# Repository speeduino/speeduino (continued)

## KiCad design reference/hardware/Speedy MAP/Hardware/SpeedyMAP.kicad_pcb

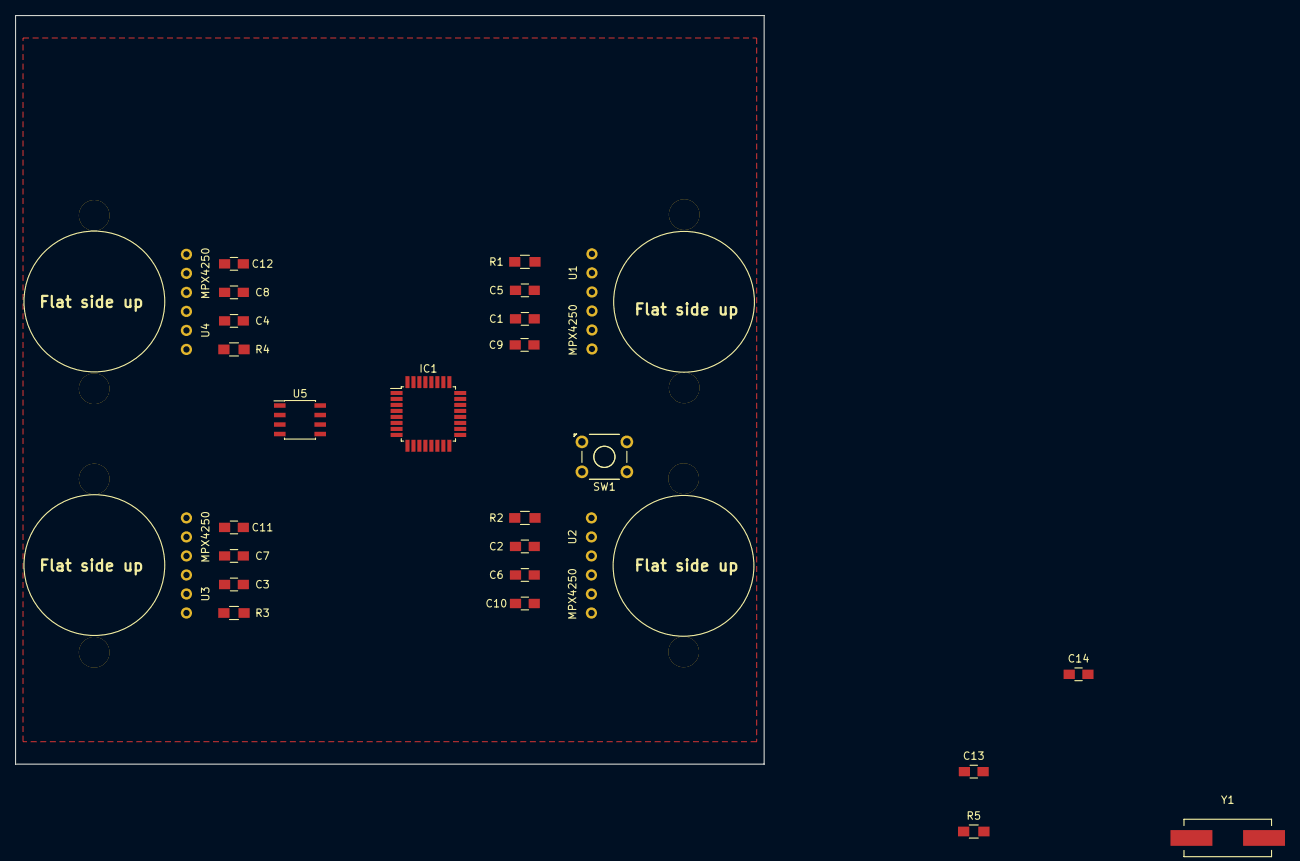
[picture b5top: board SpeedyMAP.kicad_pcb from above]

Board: 2 copper layers, 100.0 x 100.0 mm, 27 parts (0 on the bottom side), 16 nets, no tracks yet.

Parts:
C1, C2, C3, C4: C1uF; C_0805_HandSoldering
C5, C6, C7, C8: C0.01uF; C_0805_HandSoldering
C9, C10, C11, C12: C0.3uF; C_0805_HandSoldering
C13, C14: C22pF; C_0805_HandSoldering
IC1: ATMEGA328-A; TQFP-32_7x7mm_Pitch0.8mm
R1, R2, R3, R4: R750; R_0805_HandSoldering
R5: R10k; R_0805_HandSoldering
SW1: SW_SPST; SW_TH_Tactile_Omron_B3F-10xx
U1, U2, U3, U4: MPX4250
U5: MCP4921-E/SN; SOIC-8_3.9x4.9mm_Pitch1.27mm
Y1: Crystal; Crystal_HC49-SD_SMD

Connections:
+5V: C1.1, C2.1, C3.1, C4.1, C5.1, C6.1, C7.1, C8.1, IC1.4, IC1.6, R5.1, U1.3, U2.3, U3.3, U4.3, U5.1, U5.6
DAC_SS: IC1.14, U5.2
DAC_Serial: IC1.15, U5.4
GND: C1.2, C2.2, C3.2, C4.2, C5.2, C6.2, C7.2, C8.2, C9.2, C10.2, C11.2, C12.2, C13.1, C14.1, IC1.3, IC1.5, IC1.21, SW1.2, U1.2, U2.2, U3.2, U4.2, U5.5, U5.7
MAP1: C9.1, IC1.23, R1.1
MAP2: C10.1, IC1.24, R2.1
MAP3: C11.1, IC1.25, R3.1
MAP4: C12.1, IC1.26, R4.1
unnamed: C13.2, IC1.7, Y1.1
unnamed: C14.2, IC1.8, Y1.2
unnamed: IC1.29, R5.2, SW1.1
unnamed: R1.2, U1.1
unnamed: R2.2, U2.1
unnamed: R3.2, U3.1
unnamed: R4.2, U4.1
SCK: IC1.17, U5.3

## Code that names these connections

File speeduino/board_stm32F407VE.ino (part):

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    stimer_t HardwareTimers_4;
    stimer_t HardwareTimers_5;
    stimer_t HardwareTimers_8;
    #define LED_BUILTIN PA7
    //These should really be in the stm32GENERIC libs, but for somereason they only have timers 1-4
//    #include <stm32_TIM_variant_11.h>
//      #include "src/HardwareTimers/HardwareTimer.h"
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      //Black F407VE http://wiki.stm32duino.com/index.php?title=STM32F407
      //PC8~PC12 SDio

      //PA9..PA10 Serial1
      //PA11..PA12 USB
      //PA13..PA15 & PB4 SWD(debug) pins
      //PB0 EEPROM CS pin
      //PB1 LCD
      //PB2 BOOT1 
      //PB3..PB5 SPI interface
      //PB6..PB8 NRF interface

      //PD5 & PD6 Serial2
      pinInjector1 = PA1; //Output pin injector 1 is on
      pinInjector2 = PA2; //Output pin injector 2 is on
      pinInjector3 = PA3; //Output pin injector 3 is on
      pinInjector4 = PA4; //Output pin injector 4 is on
      pinInjector5 = PA5; //Output pin injector 5 is on
      pinInjector6 = PD4; //Output pin injector 6 is on
      pinCoil1 = PD7; //Pin for coil 1
      pinCoil2 = PB9; //Pin for coil 2
      pinCoil3 = PA8; //Pin for coil 3
      pinCoil4 = PB10; //Pin for coil 4
      pinCoil5 = PB11; //Pin for coil 5
      pinMAP = PC0; //MAP sensor pin
      pinTPS = PC1;//TPS input pin
      pinIAT = PC2; //IAT sensor pin
      pinCLT = PC3; //CLS sensor pin
      pinO2 = PC5; //O2 Sensor pin
      pinBat = PB1; //Battery reference voltage pin
      pinBaro = PC4;
      pinIdle1 = PB12; //Single wire idle control
      pinIdle2 = PB11; //2 wire idle control
      pinBoost = PC7; //Boost control
      pinVVT_1 = PD3; //Default VVT output
      pinStepperDir = PE0; //Direction pin  for DRV8825 driver
      pinStepperStep = PE1; //Step pin for DRV8825 driver
      pinStepperEnable = PE2; //Enable pin for DRV8825
      pinDisplayReset = PE5; // OLED reset pin
      pinFan = PE6; //Pin for the fan output

      pinFuelPump = PA6; //Fuel pump output
      pinTachOut = PD15; //Tacho output pin
      // pinLaunch = 51; //Can be overwritten below
      // pinResetControl = 43; //Reset control output

      //external interrupt enabled pins
      //external interrupts could be enalbed in any pin, except same port numbers (PA4,PE4)
      pinFlex = PD4; // Flex sensor (Must be external interrupt enabled)
      pinTrigger = PD13; //The CAS pin
      pinTrigger2 = PD14; //The Cam Sensor pin
      break;
    case 1:
      //Pin mappings as per the v0.4 shield
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      //Black F407VE http://wiki.stm32duino.com/index.php?title=STM32F407
      //PC8~PC12 SDio

      //PA9..PA10 Serial1
      //PA11..PA12 USB
      //PA13..PA15 & PB4 SWD(debug) pins
      //PB0 EEPROM CS pin
      //PB1 LCD
      //PB2 BOOT1 
      //PB3..PB5 SPI interface
      //PB6..PB8 NRF interface

      //PD5 & PD6 Serial2
      pinInjector1 = PA1; //Output pin injector 1 is on
      pinInjector2 = PA2; //Output pin injector 2 is on
      pinInjector3 = PA3; //Output pin injector 3 is on
      pinInjector4 = PA4; //Output pin injector 4 is on
      pinInjector5 = PA5; //Output pin injector 5 is on
      pinInjector6 = PD4; //Output pin injector 6 is on
      pinCoil1 = PD7; //Pin for coil 1
      pinCoil2 = PB9; //Pin for coil 2
      pinCoil3 = PA8; //Pin for coil 3
      pinCoil4 = PB10; //Pin for coil 4
      pinCoil5 = PB11; //Pin for coil 5
      pinMAP = PC0; //MAP sensor pin
      pinTPS = PC1;//TPS input pin
      pinIAT = PC2; //IAT sensor pin
      pinCLT = PC3; //CLS sensor pin
      pinO2 = PC5; //O2 Sensor pin
      pinBat = PB1; //Battery reference voltage pin
      pinBaro = PC4;
      pinIdle1 = PB12; //Single wire idle control
      pinIdle2 = PB11; //2 wire idle control
      pinBoost = PC7; //Boost control
      pinVVT_1 = PD3; //Default VVT output
      pinStepperDir = PE0; //Direction pin  for DRV8825 driver
      pinStepperStep = PE1; //Step pin for DRV8825 driver
      pinStepperEnable = PE2; //Enable pin for DRV8825
      pinDisplayReset = PE5; // OLED reset pin
      pinFan = PE6; //Pin for the fan output

      pinFuelPump = PA6; //Fuel pump output
      pinTachOut = PD15; //Tacho output pin
      // pinLaunch = 51; //Can be overwritten below
      // pinResetControl = 43; //Reset control output

      //external interrupt enabled pins
      //external interrupts could be enalbed in any pin, except same port numbers (PA4,PE4)
      pinFlex = PD4; // Flex sensor (Must be external interrupt enabled)
      pinTrigger = PD13; //The CAS pin
      pinTrigger2 = PD14; //The Cam Sensor pin
      break;
  
    case 2:
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      //Black F407VE http://wiki.stm32duino.com/index.php?title=STM32F407
      //PC8~PC12 SDio

      //PA9..PA10 Serial1
      //PA11..PA12 USB
      //PA13..PA15 & PB4 SWD(debug) pins
      //PB0 EEPROM CS pin
      //PB1 LCD
      //PB2 BOOT1 
      //PB3..PB5 SPI interface
      //PB6..PB8 NRF interface

      //PD5 & PD6 Serial2
      pinInjector1 = PA1; //Output pin injector 1 is on
      pinInjector2 = PA2; //Output pin injector 2 is on
      pinInjector3 = PA3; //Output pin injector 3 is on
      pinInjector4 = PA4; //Output pin injector 4 is on
      pinInjector5 = PA5; //Output pin injector 5 is on
      pinInjector6 = PD4; //Output pin injector 6 is on
      pinCoil1 = PD7; //Pin for coil 1
      pinCoil2 = PB9; //Pin for coil 2
      pinCoil3 = PA8; //Pin for coil 3
      pinCoil4 = PB10; //Pin for coil 4
      pinCoil5 = PB11; //Pin for coil 5
      pinMAP = PC0; //MAP sensor pin
      pinTPS = PC1;//TPS input pin
      pinIAT = PC2; //IAT sensor pin
      pinCLT = PC3; //CLS sensor pin
      pinO2 = PC5; //O2 Sensor pin
      pinBat = PB1; //Battery reference voltage pin
      pinBaro = PC4;
      pinIdle1 = PB12; //Single wire idle control
      pinIdle2 = PB11; //2 wire idle control
      pinBoost = PC7; //Boost control
      pinVVT_1 = PD3; //Default VVT output
      pinStepperDir = PE0; //Direction pin  for DRV8825 driver
      pinStepperStep = PE1; //Step pin for DRV8825 driver
      pinStepperEnable = PE2; //Enable pin for DRV8825
      pinDisplayReset = PE5; // OLED reset pin
      pinFan = PE6; //Pin for the fan output

      pinFuelPump = PA6; //Fuel pump output
      pinTachOut = PD15; //Tacho output pin
      // pinLaunch = 51; //Can be overwritten below
      // pinResetControl = 43; //Reset control output

      //external interrupt enabled pins
      //external interrupts could be enalbed in any pin, except same port numbers (PA4,PE4)
      pinFlex = PD4; // Flex sensor (Must be external interrupt enabled)
      pinTrigger = PD13; //The CAS pin
      pinTrigger2 = PD14; //The Cam Sensor pin
      break;

    case 3:
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      //Black F407VE http://wiki.stm32duino.com/index.php?title=STM32F407
      //PC8~PC12 SDio

      //PA9..PA10 Serial1
      //PA11..PA12 USB
      //PA13..PA15 & PB4 SWD(debug) pins
      //PB0 EEPROM CS pin
      //PB1 LCD
      //PB2 BOOT1 
      //PB3..PB5 SPI interface
      //PB6..PB8 NRF interface

      //PD5 & PD6 Serial2
      pinInjector1 = PA1; //Output pin injector 1 is on
      pinInjector2 = PA2; //Output pin injector 2 is on
      pinInjector3 = PA3; //Output pin injector 3 is on
      pinInjector4 = PA4; //Output pin injector 4 is on
      pinInjector5 = PA5; //Output pin injector 5 is on
      pinInjector6 = PD4; //Output pin injector 6 is on
      pinCoil1 = PD7; //Pin for coil 1
      pinCoil2 = PB9; //Pin for coil 2
      pinCoil3 = PA8; //Pin for coil 3
      pinCoil4 = PB10; //Pin for coil 4
      pinCoil5 = PB11; //Pin for coil 5
      pinMAP = PC0; //MAP sensor pin
      pinTPS = PC1;//TPS input pin
      pinIAT = PC2; //IAT sensor pin
      pinCLT = PC3; //CLS sensor pin
      pinO2 = PC5; //O2 Sensor pin
      pinBat = PB1; //Battery reference voltage pin
      pinBaro = PC4;
      pinIdle1 = PB12; //Single wire idle control
      pinIdle2 = PB11; //2 wire idle control
      pinBoost = PC7; //Boost control
      pinVVT_1 = PD3; //Default VVT output
      pinStepperDir = PE0; //Direction pin  for DRV8825 driver
      pinStepperStep = PE1; //Step pin for DRV8825 driver
      pinStepperEnable = PE2; //Enable pin for DRV8825
      pinDisplayReset = PE5; // OLED reset pin
      pinFan = PE6; //Pin for the fan output

      pinFuelPump = PA6; //Fuel pump output
      pinTachOut = PD15; //Tacho output pin
      // pinLaunch = 51; //Can be overwritten below
      // pinResetControl = 43; //Reset control output

      //external interrupt enabled pins
      //external interrupts could be enalbed in any pin, except same port numbers (PA4,PE4)
      pinFlex = PD4; // Flex sensor (Must be external interrupt enabled)
      pinTrigger = PD13; //The CAS pin
      pinTrigger2 = PD14; //The Cam Sensor pin
      break;

    case 9:
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      pinCoil3 = 32; //Pin for coil 3
      pinCoil4 = 33; //Pin for coil 4
      pinCoil5 = 34; //Pin for coil 5 PLACEHOLDER value for now
      pinTrigger = 19; //The CAS pin
      pinTrigger2 = 18; //The Cam Sensor pin
      pinTPS = A2;//TPS input pin
      pinMAP = A5; //MAP sensor pin
      pinIAT = A0; //IAT sensor pin
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
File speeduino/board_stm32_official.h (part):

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    #define NUM_DIGITAL_PINS 35
  #endif
  #ifndef LED_BUILTIN
    #define LED_BUILTIN PB1 //Maple Mini
  #endif
#elif defined(STM32F407xx)
  #ifndef NUM_DIGITAL_PINS
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
//When building for Black board Serial1 is instantiated,building generic STM32F4x7 has serial2 and serial 1 must be done here
#if SERIAL_UART_INSTANCE==2
HardwareSerial Serial1(PA10, PA9);
#endif

extern STM32RTC& rtc;
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  static inline bool pinIsReserved(uint8_t pin) { 
    return (pin == (uint8_t)PA11) 
        || (pin == (uint8_t)PA12) 
        || (pin == (uint8_t)PC14) 
        || (pin == (uint8_t)PC15)
      ;
  }

  #ifndef PB11 //Hack for F4 BlackPills
    #define PB11 PB10
  #endif
  //Hack to allow compilation on small STM boards
  #ifndef A10
    #define A10  PA0
    #define A11  PA1
    #define A12  PA2
    #define A13  PA3
    #define A14  PA4
    #define A15  PA5
  #endif
#else
  #ifdef USE_SPI_EEPROM
    #if defined(BOARD_FCR_MICRO_F4) //FCR Micro F4: USB(PA11/PA12) + VBUS sense(PA9) + SPI3 flash(PC10/11/12) + CS + CAN1 ALT_2(PD0/PD1)
    static inline bool pinIsReserved(uint8_t pin) {
      PinName p = digitalPinToPinName(pin);
      return (p == PA_11)
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    static inline bool pinIsReserved(uint8_t pin) {
      return (pin == (uint8_t)PA11)
          || (pin == (uint8_t)PA12)
          || (pin == (uint8_t)PB3)
          || (pin == (uint8_t)PB4)
          || (pin == (uint8_t)USE_SPI_EEPROM)
        ;
    }
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    static inline bool pinIsReserved(uint8_t pin) { 
      return (pin == (uint8_t)PA11) 
          || (pin == (uint8_t)PA12)
          || (pin == (uint8_t)PB3) 
          || (pin == (uint8_t)PB4)
          || (pin == (uint8_t)PB5)
          || (pin == (uint8_t)PB0)
         ;
    }
  #endif
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#define PWM_FAN_AVAILABLE

#ifndef LED_BUILTIN
  #define LED_BUILTIN PA7
#endif

/*
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
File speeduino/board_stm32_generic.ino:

#if defined(CORE_STM32_GENERIC)
  #include "board_stm32_generic.h"
  #include "globals.h"
  #include "auxiliaries.h"
  #include "idle.h"
  #include "scheduler.h"
  #include "HardwareTimer.h"

  #if defined(FRAM_AS_EEPROM)
    #if defined(STM32F407xx)
FramClass EEPROM(PB5, PB4, PB3, PB0); /*(mosi, miso, sclk, ssel, clockspeed) 31/01/2020*/
    #else
FramClass EEPROM(PB15, PB14, PB13, PB12); // Blue/Black Pills
    #endif
  #endif

void initBoard()
{
  /*
  ***********************************************************************************************************
  * General
  */
  #ifndef FLASH_LENGTH
    #define FLASH_LENGTH 8192
  #endif
  delay(10);
  /*
  ***********************************************************************************************************
  * Idle
  */
  if((configPage6.iacAlgorithm == IAC_ALGORITHM_PWM_OL) || (configPage6.iacAlgorithm == IAC_ALGORITHM_PWM_CL))
  {
    idle_pwm_max_count = 1000000L / (TIMER_RESOLUTION * configPage6.idleFreq * 2); // Converts the frequency in Hz to the number of ticks (at 2uS) it takes to complete 1 cycle. Note that the frequency is divided by 2 coming from TS to allow for up to 5KHz
  }

  // This must happen at the end of the idle init
  Timer1.setMode(4, TIMER_OUTPUT_COMPARE);
  Timer1.attachInterrupt(4, idleInterrupt); // on first flash the configPage4.iacAlgorithm is invalid

  /*
  ***********************************************************************************************************
  * Timers
  */
  #if defined(ARDUINO_BLUEPILL_F103C8) || defined(ARDUINO_BLUEPILL_F103CB)
  Timer4.setPeriod(1000); // Set up period
  Timer4.setMode(1, TIMER_OUTPUT_COMPARE);
  Timer4.attachInterrupt(1, oneMSInterval);
  Timer4.resume(); // Start Timer
  #else
  Timer11.setPeriod(1000); // Set up period
  Timer11.setMode(1, TIMER_OUTPUT_COMPARE);
  Timer11.attachInterrupt(1, oneMSInterval);
  Timer11.resume(); // Start Timer
  #endif
  pinMode(LED_BUILTIN, OUTPUT); // Visual WDT

  /*
  ***********************************************************************************************************
  * Auxiliaries
  */
  // 2uS resolution Min 8Hz, Max 5KHz
  boost_pwm_max_count = 1000000L / (TIMER_RESOLUTION * configPage6.boostFreq * 2); // Converts the frequency in Hz to the number of ticks (at 2uS) it takes to complete 1 cycle. The x2 is there because the frequency is stored at half value (in a byte) to allow frequencies up to 511Hz
  vvt_pwm_max_count   = 1000000L / (TIMER_RESOLUTION * configPage6.vvtFreq * 2);   // Converts the frequency in Hz to the number of ticks (at 2uS) it takes to complete 1 cycle
  fan_pwm_max_count   = 1000000L / (TIMER_RESOLUTION * configPage6.fanFreq * 2);   // Converts the frequency in Hz to the number of ticks (at 4uS) it takes to complete 1 cycle

  // Need to be initialised last due to instant interrupt
  Timer1.setMode(1, TIMER_OUTPUT_COMPARE);
  Timer1.setMode(2, TIMER_OUTPUT_COMPARE);
  Timer1.setMode(3, TIMER_OUTPUT_COMPARE);
  Timer1.attachInterrupt(1, fanInterrupt);
  Timer1.attachInterrupt(2, boostInterrupt);
  Timer1.attachInterrupt(3, vvtInterrupt);

  /*
  ***********************************************************************************************************
  * Schedules
  */
  #if defined(ARDUINO_BLUEPILL_F103C8) || defined(ARDUINO_BLUEPILL_F103CB)
  //(CYCLES_PER_MICROSECOND == 72, APB2 at 72MHz, APB1 at 36MHz).
  // Timer2 to 4 is on APB1, Timer1 on APB2.   www.st.com/resource/en/datasheet/stm32f103cb.pdf sheet 12
  Timer1.setPrescaleFactor(((Timer1.getBaseFrequency() / 1000000) * TIMER_RESOLUTION) - 1); // 2us resolution
  Timer2.setPrescaleFactor(((Timer2.getBaseFrequency() / 1000000) * TIMER_RESOLUTION) - 1); // 2us resolution
  Timer3.setPrescaleFactor(((Timer3.getBaseFrequency() / 1000000) * TIMER_RESOLUTION) - 1); // 2us resolution
  #else
  //(CYCLES_PER_MICROSECOND == 168, APB2 at 84MHz, APB1 at 42MHz).
  // Timer2 to 14 is on APB1, Timers 1, 8, 9 and 10 on APB2.   www.st.com/resource/en/datasheet/stm32f407vg.pdf sheet 120
  Timer1.setPrescaleFactor(((Timer1.getBaseFrequency() / 1000000) * TIMER_RESOLUTION) - 1); // 2us resolution
  Timer2.setPrescaleFactor(((Timer2.getBaseFrequency() / 1000000) * TIMER_RESOLUTION) - 1); // 2us resolution
  Timer3.setPrescaleFactor(((Timer3.getBaseFrequency() / 1000000) * TIMER_RESOLUTION) - 1); // 2us resolution
  Timer4.setPrescaleFactor(((Timer4.getBaseFrequency() / 1000000) * TIMER_RESOLUTION) - 1); // 2us resolution
  Timer5.setPrescaleFactor(((Timer5.getBaseFrequency() / 1000000) * TIMER_RESOLUTION) - 1); // 2us resolution
  #endif
  Timer2.setMode(1, TIMER_OUTPUT_COMPARE);
  Timer2.setMode(2, TIMER_OUTPUT_COMPARE);
  Timer2.setMode(3, TIMER_OUTPUT_COMPARE);
  Timer2.setMode(4, TIMER_OUTPUT_COMPARE);

  Timer3.setMode(1, TIMER_OUTPUT_COMPARE);
  Timer3.setMode(2, TIMER_OUTPUT_COMPARE);
  Timer3.setMode(3, TIMER_OUTPUT_COMPARE);
  Timer3.setMode(4, TIMER_OUTPUT_COMPARE);

  // Attach interrupt functions
  // Injection
  Timer2.attachInterrupt(1, fuelSchedule1Interrupt);
  Timer2.attachInterrupt(2, fuelSchedule2Interrupt);
  Timer2.attachInterrupt(3, fuelSchedule3Interrupt);
  Timer2.attachInterrupt(4, fuelSchedule4Interrupt);
  #if(INJ_CHANNELS >= 5)
  Timer5.setMode(1, TIMER_OUTPUT_COMPARE);
  Timer5.attachInterrupt(1, fuelSchedule5Interrupt);
  #endif
  #if(INJ_CHANNELS >= 6)
  Timer5.setMode(2, TIMER_OUTPUT_COMPARE);
  Timer5.attachInterrupt(2, fuelSchedule6Interrupt);
  #endif
  #if(INJ_CHANNELS >= 7)
  Timer5.setMode(3, TIMER_OUTPUT_COMPARE);
  Timer5.attachInterrupt(3, fuelSchedule7Interrupt);
  #endif
  #if(INJ_CHANNELS >= 8)
  Timer5.setMode(4, TIMER_OUTPUT_COMPARE);
  Timer5.attachInterrupt(4, fuelSchedule8Interrupt);
  #endif

  // Ignition
  Timer3.attachInterrupt(1, ignitionSchedule1Interrupt);
  Timer3.attachInterrupt(2, ignitionSchedule2Interrupt);
  Timer3.attachInterrupt(3, ignitionSchedule3Interrupt);
  Timer3.attachInterrupt(4, ignitionSchedule4Interrupt);
  #if(IGN_CHANNELS >= 5)
  Timer4.setMode(1, TIMER_OUTPUT_COMPARE);
  Timer4.attachInterrupt(1, ignitionSchedule5Interrupt);
  #endif
  #if(IGN_CHANNELS >= 6)
  Timer4.setMode(2, TIMER_OUTPUT_COMPARE);
  Timer4.attachInterrupt(2, ignitionSchedule6Interrupt);
  #endif
  #if(IGN_CHANNELS >= 7)
  Timer4.setMode(3, TIMER_OUTPUT_COMPARE);
  Timer4.attachInterrupt(3, ignitionSchedule7Interrupt);
  #endif
  #if(IGN_CHANNELS >= 8)
  Timer4.setMode(4, TIMER_OUTPUT_COMPARE);
  Timer4.attachInterrupt(4, ignitionSchedule8Interrupt);
  #endif

  Timer1.setOverflow(0xFFFF);
  Timer1.resume();
  Timer2.setOverflow(0xFFFF);
  Timer2.resume();
  Timer3.setOverflow(0xFFFF);
  Timer3.resume();
  #if(IGN_CHANNELS >= 5)
  Timer4.setOverflow(0xFFFF);
  Timer4.resume();
  #endif
  #if(INJ_CHANNELS >= 5)
  Timer5.setOverflow(0xFFFF);
  Timer5.resume();
  #endif
}

uint16_t freeRam()
{
  char top = 't';
  return &top - reinterpret_cast<char *>(sbrk(0));
}

void doSystemReset(void)
{
  __disable_irq();
  NVIC_SystemReset();
}

void jumpToBootloader(void) // https://github.com/3devo/Arduino_Core_STM32/blob/jumpSysBL/libraries/SrcWrapper/src/stm32/bootloader.c
{                           // https://github.com/markusgritsch/SilF4ware/blob/master/SilF4ware/drv_reset.c
  HAL_RCC_DeInit();
  HAL_DeInit();
  SysTick->VAL = SysTick->LOAD = SysTick->CTRL = 0;
  SYSCFG->MEMRMP                               = 0x01;

  #if defined(STM32F7xx) || defined(STM32H7xx)
  const uint32_t DFU_addr = 0x1FF00000; // From AN2606
  #else
  const uint32_t DFU_addr = 0x1FFF0000;                                                     // Default for STM32F10xxx and STM32F40xxx/STM32F41xxx from AN2606
  #endif
  // This is assembly to prevent modifying the stack pointer after
  // loading it, and to ensure a jump (not call) to the bootloader.
  // Not sure if the barriers are really needed, they were taken from
  // https://github.com/GrumpyOldPizza/arduino-STM32L4/blob/ac659033eadd50cfe001ba1590a1362b2d87bb76/system/STM32L4xx/Source/boot_stm32l4xx.c#L159-L165
  asm volatile("ldr r0, [%[DFU_addr], #0]   \n\t" // get address of stack pointer
               "msr msp, r0            \n\t"      // set stack pointer
               "ldr r0, [%[DFU_addr], #4]   \n\t" // get address of reset handler
               "dsb                    \n\t"      // data sync barrier
               "isb                    \n\t"      // instruction sync barrier
               "bx r0                  \n\t"      // branch to bootloader
               :
               : [DFU_addr] "l"(DFU_addr)
               : "r0");
  __builtin_unreachable();
}

#endif
